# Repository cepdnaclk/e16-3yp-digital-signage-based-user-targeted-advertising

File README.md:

# Project Name : Digital Signage Based User Targeted Advertising

[**Click here to visit our website**](https://cepdnaclk.github.io/e16-3yp-digital-signage-based-user-targeted-advertising/)

## INTRODUCTION

Digital signage is one of the best platforms to play advertisements nowadays. The network of digital displays that are managed from a central position and shows dynamically changing content is known as digital advertising.

Main usage purposes of digital signage is for promoting products,attention grabbing content, public information systems etc. Digital advertising can be seen in many places like supermarkets, shopping malls, bus stations, clothing stores and restaurants. Advantages that come with this system are ability to deliver information to people,easy to reach a large number of crowds at once, display some attention grabbing content and reduced cost.

## PROBLEM
Most of the advertisements displayed in the digital screens are not relevant for the targeted audience. So,ninety percent of the advertisements displayed using the currently existing digital signages are not very effective. Also the provided digital signage solutions are expensive to afford for most of the SMEs(Small and Medium Enterprises). So overcoming these problems with an improved device for an affordable price will have a good market value.

## SOLUTION
To overcome this kind of issues our proposed solution consists of an upgraded version with additional hardware/software which can do User Targeted Advertising. Here our aim is while showing content that changes dynamically, when a particular crowd (male/female/group) is identified in front of the screens it will change the current content flow and show some relevant,interesting advertisement for the targeted audience that might catch their attention.

The buyer(shop owner) of the digital signage unit can upload their advertisements using the provided user authenticated mobile application. Also add some specific advertisements categorized by gender and age group. When a user in front is detected specific content will be visible to the targeted audience.

Our solution architecture mainly consists of three units. They are digital signage control unit , user detecting and analysing unit and the smart power supply unit.

## PROPOSED SYSTEM : METHODOLOGY 

The system consists of raspberry pi 3 which will act as the heart of the system and flutter as the mobile application framework for the front end and firestore as the backend.

In the processes of user targeting, the User Detecting and Analyzing Unit recognizes the person in front of it  as a male or female.  Then approximate the age of that person. If there are more than one people, the system recognizes all the people. Here to take the live camera feed to the system, Raspberry PI camera module is used and to predict the age and the gender pre-trained machine learning and deep learning models with OpenCV are used.  
 
The Digital display is connected to raspberry pi using HDMI and the User Detecting and Analyzing Unit is attached to the digital display. This  mainly consists of Raspberry PI camera module. OpenCV library is used since it consists of algorithms for easy face detection and gender & age classification.

For face detection a lightweight and speed machine learning  algorithm called Haar Cascades is used. Even Though there are more accurate methods such as  HOG + Linear SVM, Single Shot Detectors and deep learning-based face detectors, haar cascades classifier is used due to its ability to rapid object detection and its high speed. For gender and age predicting, a pre-trained deep learning model is used. (Caffe model trained by Levi and Hassner in 2015)

- Firebase is used as the web server as it provides a number of economical and flexible features. 
- Flutter is used as the mobile app framework where dart is used as the programming language since the same code base can be used to develop both android and ios applications.

#### App front end designs

<div id = "app_frontends_list1" style="margin-bottom: 3em;">
    <div class="inline-block">
           
    </div>
   <div class="inline-block">
           
        </div> 
 <div class="inline-block">
           
        </div>
  <div class="inline-block">
        
    </div>
</div>

<div id = "app_frontends_list2">
    <div class="inline-block">
           
    </div>  
    <div class="inline-block">
           
        </div> 
    <div class="inline-block">
           
       </div>
    <div class="inline-block">
        
    </div>
</div>

#### Smart Power Supply Unit
As an additional improvement, a smart power supply unit which can control the digital screen is implemented.
The system consists of a Smart Power Supply Unit that can be controlled through the internet from anywhere. It connects through the mobile app and the shopkeepers can control the screen anytime they want. Here, MQTT which is a lightweight protocol is used to communicate with the nodeMCU that has been placed inside the Smart Power Supply Unit. Using publish/subscribe and using the MacAddresses for topics each device can be uniquely identified and publish on/off messages to the device to control the digital screen by switching the relay inside. 
Here is the hardware design implementation diagrams for the smart power supply unit

#### Testing units
Multiple tests have driven to ensure the accurate functionality of the product. A detailed summary is provided in the webpage. A brief explaination about some of the validations and optimization through tests are as below
  * Check face detection and age/gender predicton accuracy when multiple people detected in a frame 
  * User entry validations for invalid form fills in login and profile pages  
  * Validating each users MacAddresses from firestore retrieve.
  * Devices add/drop functionality and drop down menu in app syncing with firestore collections
  * Subscribing to specific MacAddress topic and reconnecting in wifi failure with last published message status capturing

#### Bill of materials

## Documentation
> [Design Manual](https://github.com/cepdnaclk/e16-3yp-digital-signage-based-user-targeted-advertising/blob/main/Documentation/Design%20Manual%20-%20Digital%20Signage%20Based%20User%20Targeted%20Advertising%20(1).pdf) 

> [User Manual](https://github.com/cepdnaclk/e16-3yp-digital-signage-based-user-targeted-advertising/blob/main/Documentation/User%20Manual%20-%20Digital%20Signage%20Based%20User%20Targeted%20Advertising%20(1).pdf) 

## Advisors

>Dr. Isuru Nawinne

##### Links:
> [Department of Computer Engineering Website](http://www.ce.pdn.ac.lk/) 

> [Faculty of Engineering Website](https://eng.pdn.ac.lk/) 

> [University of Peradeniya Website](https://www.pdn.ac.lk/)

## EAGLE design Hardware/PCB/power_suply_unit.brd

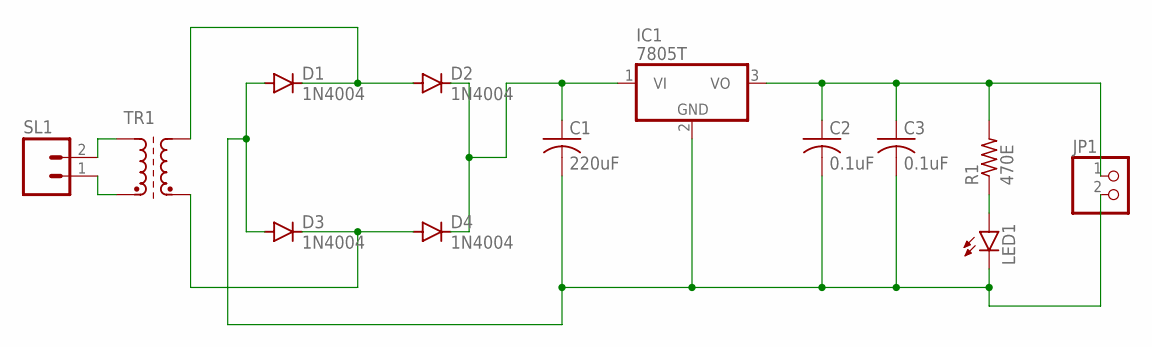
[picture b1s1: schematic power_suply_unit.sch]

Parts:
C1: 220uF; C025-024X044
C2, C3: 0.1uF; C025-024X044
D1, D2, D3, D4: 1N4004; DO41-10
IC1: 7805T; TO220H
JP1: PINHD-1X2; 1X02
LED1: LED3MM
R1: 470E; 0204/7
SL1: M02; 02P
TR1: SM-T4

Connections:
unnamed: SL1.2, TR1.1 (A1)
unnamed: SL1.1, TR1.2 (E1)
unnamed: D1.C, D2.A, TR1.5 (A2)
unnamed: D3.C, D4.A, TR1.4 (E2)
unnamed: C1.1, D2.C, D4.C, IC1.1 (VI)
unnamed: LED1.A, R1.1
unnamed: C2.1, C3.1, IC1.3 (VO), JP1.1, R1.2
unnamed: C1.2, C2.2, C3.2, D1.A, D3.A, IC1.2 (GND), JP1.2, LED1.K (C)

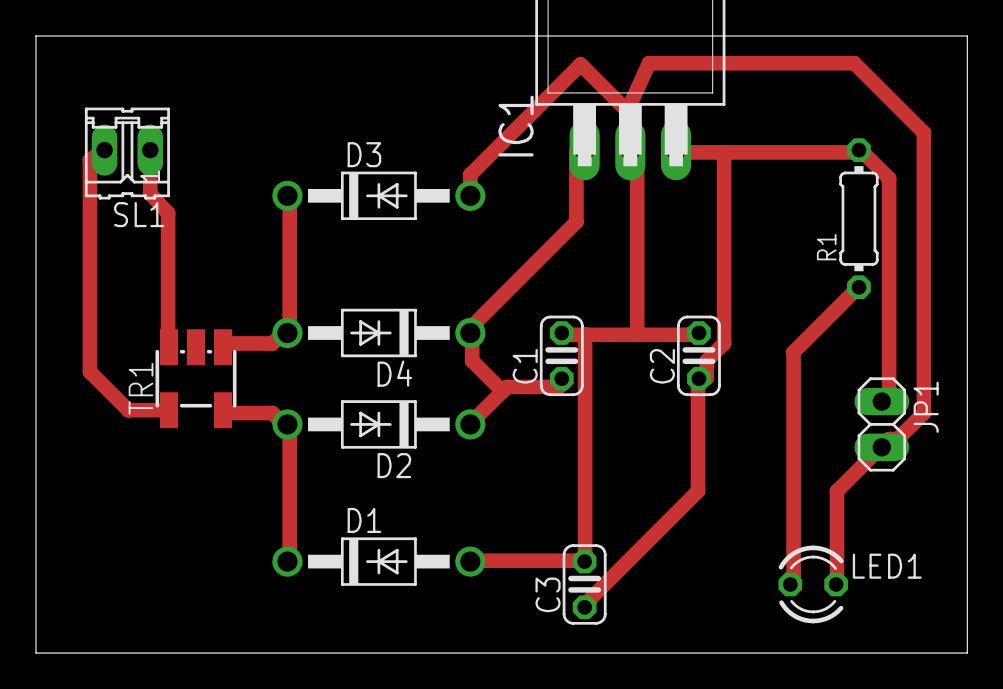
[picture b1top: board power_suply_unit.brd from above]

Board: 2 copper layers, 51.7 x 34.3 mm, 13 parts (0 on the bottom side), 8 nets.

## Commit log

2020-10-17 Update README.md
    Project Name : Digital Signage Based User Targeted Advertising
    Group Members : E/16/083 - e16083@eng.pdn.ac.lk
    E/16/368 - e16368@eng.pdn.ac.lk
    E/16/200 - e16200@eng.pdn.ac.lk
2020-10-17 Image folder added
2020-10-17 intro image added
2020-10-17 doc folder added
2020-10-17 Set theme jekyll-theme-cayman
2020-10-17 Set theme jekyll-theme-modernist
2020-10-17 Set theme jekyll-theme-minimal
2020-10-17 Links added to README.md
2020-10-18 imgs added
2020-11-02 Add files via upload
    picture of bill of materials
2020-11-02 Update README.md
    added the budget details
2020-11-02 Members pics added
2020-11-02 Members images added
2020-11-02 Updated with web page link
2020-11-02 updated github page
2020-11-02 github repo link added
2020-11-04 web page
2020-11-04 modified
2020-11-04 Title updated
2020-11-04 updated github repo description
2020-11-04 ER diagram was added to the web page
2020-11-05 Create CNAME
2020-11-05 changed er model
2020-11-05 circuit added
2020-11-05 new images added
2020-11-05 Allignments were changed
2020-11-06 structure added
2020-11-06 cname deleted
2020-11-06 block diagram added
2020-11-07 block diagram updated
2020-11-07 User detecting code updated
2020-11-07 Instructions updated,comments added
2020-11-08 circuit updated
2020-11-08 Fritzing files
2020-11-08 soft diagrams added
2020-11-08 python code added
2020-11-08 codes updated
2020-11-08 flutter initialized
2020-11-08 user targeted advertisng added
2020-11-08 changes to page
2020-11-08 UI designs added
2020-11-11 UI diagrams modified
2020-11-11 pages added
2020-11-11 done
2021-01-25 smart power supply unit
2021-01-28 project app added with firestore testing
2021-01-28 project app phone auth added
2021-01-29 project app use targeting interface added
2021-01-30 App code updated
2021-01-30 project app advertisemet linkes updated
2021-01-30 google sign in added
2021-01-30 create account added
2021-01-30 profile completed
2021-01-30 dashboard page added with previews
2021-01-30 logout bug fixed
2021-01-31 power sup added
2021-02-01 api implementation with firebase added
2021-02-01 power supply completed
2021-02-01 updated website
2021-02-01 device config added
2021-02-01 webpage updated with app frontend designs
2021-02-01 validation added
2021-02-01 new designs added
2021-02-01 new design added
2021-02-02 app code updated with tests and fixed validate issues
2021-02-02 Readme Updated with diagram
2021-02-02 final modifications added
2021-02-02 time duration updated
2021-02-02 ui improved
2021-02-03 teting
2021-02-03 test codes copied to test folder
2021-02-03 updated web
2021-02-05 minor changes added to front end
2021-02-13 webpage further updated with diagrams and testing
2021-03-03 webpage Updated
2021-03-05 component list updating
2021-03-05 updated bill of materials added
2021-03-05 app front end designs added
2021-03-05 Updated with diagrams
2021-03-05 code further optimized
2021-03-07 flowchart updated
2021-03-07 design updated
2021-03-08 UX improved
2021-03-08 bugs fixed
2021-03-08 clear texts
2021-03-08 alignment issue fixed
2021-03-09 edited web
2021-03-09 added frabrications
2021-03-10 added pcbs
2021-05-22 data flow content details updated
2021-05-22 website video updated
2021-05-22 resolve conflict
2021-05-23 web content on dataflow,process updated
2021-05-25 UI updated,design details added to website
2021-06-04 added json file
2021-06-05 added json
2021-07-15 manuals added
2022-02-15 large files removed - fabrication/documentation
